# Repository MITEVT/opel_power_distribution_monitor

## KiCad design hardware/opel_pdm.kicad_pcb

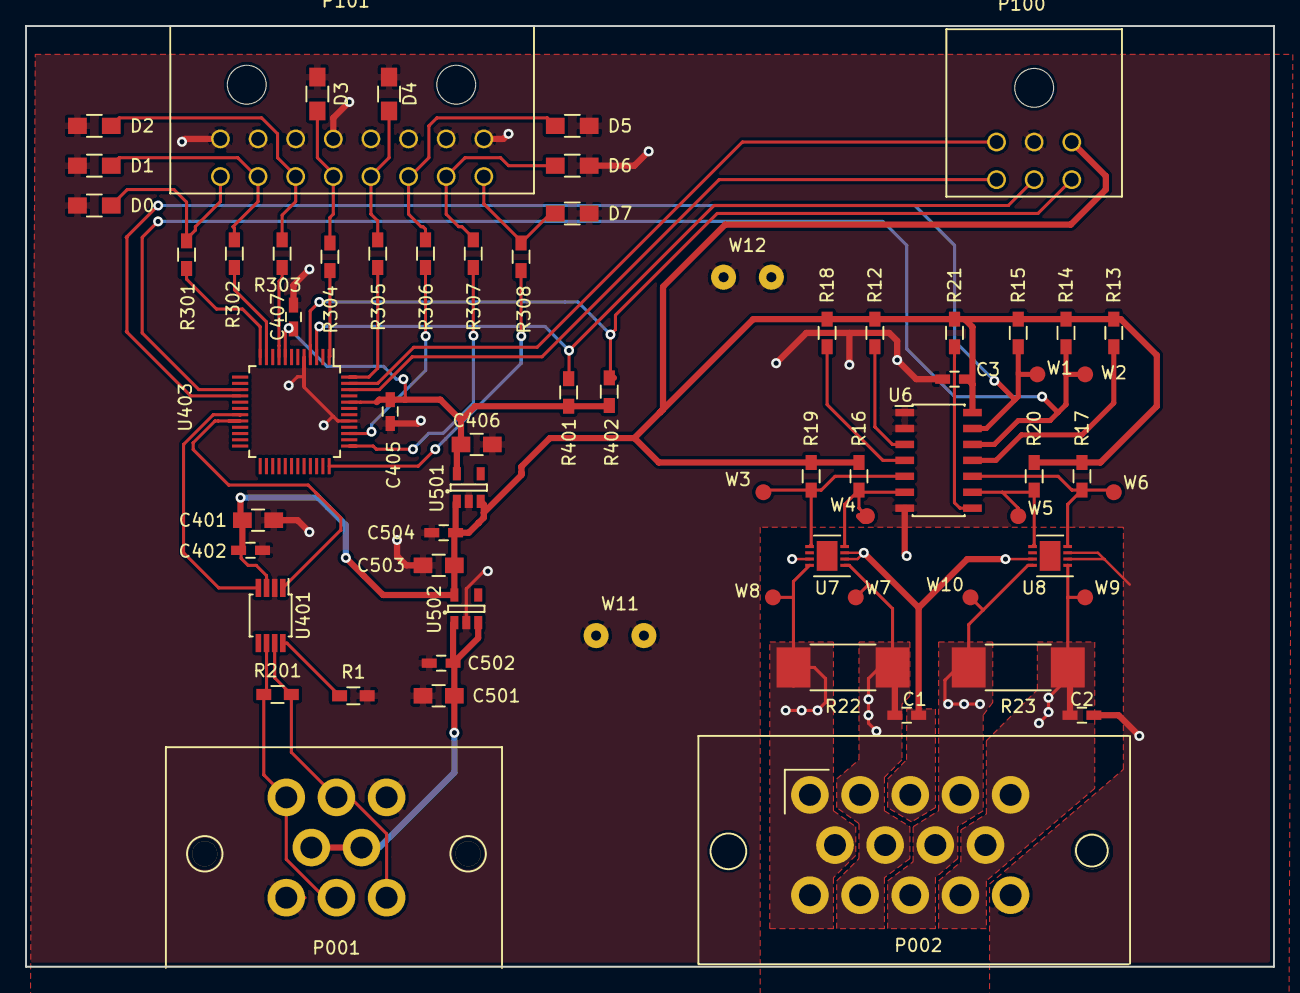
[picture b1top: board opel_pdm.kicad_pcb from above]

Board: 2 copper layers, 99.5 x 75.0 mm, 67 parts (0 on the bottom side), 43 nets.

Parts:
C1, C2: 1uF; C_0603_HandSoldering
C3, C402, C405, C407: 0.1uF; C_0603_HandSoldering
C401, C406: 10uF; C_0805_HandSoldering
C501, C503: 10μ; C_0805_HandSoldering
C502, C504: .1μ; C_0603_HandSoldering
D0: PIO2_8; R_0805_HandSoldering
D1: PIO2_7; R_0805_HandSoldering
D2: PIO1_8; R_0805_HandSoldering
D3: PIO2_6; R_0805_HandSoldering
D4: PIO3_3; R_0805_HandSoldering
D5: PIO1_3; R_0805_HandSoldering
D6: PIO3_1; R_0805_HandSoldering
D7: PIO3_0; R_0805_HandSoldering
P001: CANCONNECTOR; 776280-1
P002: CONN_01X14; 776267-1
P100: ISP; Connector_Microfit3_Header_02x03_Angled_43045-060x
P101: DEBUG_LED; Connector_Microfit3_Header_02x08_Angled_43045-160x
R1: 20k; R_0603_HandSoldering
R12, R13, R14, R15, R16, R17, R18, R19, R20, R21, R401, R402: 10k; R_0603_HandSoldering
R22, R23: 0.002; R_2512_HandSoldering
R201: 120; R_0603_HandSoldering
R301, R302, R303, R304, R305, R306, R307, R308: 100; R_0603_HandSoldering
U6: TCA9543A; SOIC-14_3.9x8.7mm_Pitch1.27mm
U7, U8: LTC2943; DFN-8-1EP_3x3mm_Pitch0.5mm
U401: MCP2551-I/SN; MSOP-8_3x3mm_Pitch0.65mm
U403: LPC11C14; LQFP-48_7x7mm_Pitch0.5mm
U501: MCP1755-33; SOT-23-5
U502: MCP1755-5; SOT-23-5
W1: SDA; smd_test_pad
W2: SCL; smd_test_pad
W3: SD0; smd_test_pad
W4: SC0; smd_test_pad
W5, W6: SD1; smd_test_pad
W7: CS+; smd_test_pad
W8: CS-; smd_test_pad
W9: LV+; smd_test_pad
W10: LV-; smd_test_pad
W11, W12: TST_GND; SolderWirePad_2x_0-8mmDrill

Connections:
+3V3: C405.1, C406.1, C407.1, R401.1, R402.1, U403.8, U403.44, U501.5
+5V: C3.1, C401.1, C402.1, C503.1, C504.1, P100.3, R12.1, R13.1, R14.1, R15.1, R16.1, R17.1, R18.1, R19.1, R20.1, R21.1, U6.14, U401.3, U501.1, U501.3, U502.5
/BACK_PANEL/CANH: P001.2, P001.8, R201.2, U401.7
/BACK_PANEL/CANL: P001.1, P001.7, R201.1, U401.6
/BACK_PANEL/CS_SENSE+: C1.1, P002.2, P002.7, P002.11, R22.1, U7.1, W7.1
/BACK_PANEL/CS_SENSE-: P002.1, P002.6, P002.10, R22.2, U7.8, W8.1
/BACK_PANEL/LV_SENSE+: C2.1, P002.5, P002.9, P002.13, R23.1, U8.1, W9.1
/BACK_PANEL/LV_SENSE-: P002.4, P002.8, P002.12, R23.2, U8.8, W10.1
/FRONT_PANEL/LED0: R301.1, U403.12
/FRONT_PANEL/LED1: R302.2, U403.11
/FRONT_PANEL/LED2: R303.2, U403.9
/FRONT_PANEL/LED3: R304.1, U403.1
/FRONT_PANEL/LED4: R305.2, U403.48
/FRONT_PANEL/LED5: R306.1, U403.39
/FRONT_PANEL/LED6: R307.2, U403.37
/FRONT_PANEL/LED7: R308.1, U403.36
/FRONT_PANEL/MCU_PROG_N: P100.6, R402.2, U403.4
/FRONT_PANEL/MCU_RESET_N: P100.5, R401.2, U403.3
/FRONT_PANEL/RXD: P100.4, U403.46
/FRONT_PANEL/TXD: P100.1, U403.47
/I2C Multiplexer and Gas Gauges/SCL: R14.2, U6.12, U403.15, W2.1
/I2C Multiplexer and Gas Gauges/SDA: R15.2, U6.13, U403.16, W1.1
/Micro_Controller/CAN_RXD: U401.4, U403.19
/Micro_Controller/CAN_TXD: U401.1, U403.20
/Power_Supplies/+12V: C501.2, C502.1, P001.4, P001.5, U502.1, U502.3
GND: C1.2, C2.2, C3.2, C401.2, C402.2, C405.2, C406.2, C407.2, C501.1, C502.2, C503.2, C504.2, D0.1, D1.1, D2.1, D3.1, D4.1, D5.1, D6.1, D7.1, P001.3, P001.6, P002.3, P002.14, P100.2, P101.1, P101.2, P101.3, P101.4, P101.5, P101.6, P101.7, P101.8, R1.2, U6.1, U6.2, U6.7, U7.2, U7.3, U7.7, U8.2, U8.3, U8.7, U401.2, U403.5, U403.41, U501.2, U502.2, W11.1, W12.1
unnamed: D0.2, P101.9, R301.2
unnamed: D1.2, P101.10, R302.1
unnamed: D2.2, P101.11, R303.1
unnamed: D3.2, P101.12, R304.2
unnamed: D4.2, P101.13, R305.1
unnamed: D5.2, P101.14, R306.2
unnamed: D6.2, P101.15, R307.1
unnamed: D7.2, P101.16, R308.2
unnamed: R1.1, U401.8
unnamed: R12.2, U6.3
unnamed: R13.2, U6.11
unnamed: R16.2, U6.6, U7.4, W4.1
unnamed: R17.2, U6.10, U8.4, W6.1
unnamed: R18.2, U6.4
unnamed: R19.2, U6.5, U7.5, W3.1
unnamed: R20.2, U6.9, U8.5, W5.1
unnamed: R21.2, U6.8

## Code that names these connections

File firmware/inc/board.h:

#ifndef __BOARD_H_
#define __BOARD_H_

#include "chip.h"
#include "util.h"
#include <string.h>

// -------------------------------------------------------------
// Global Variables

extern const uint32_t OscRateIn; 
volatile uint32_t msTicks; 						// Running count of milliseconds since start

// -------------------------------------------------------------
// Configuration Macros

typedef struct {
	bool low_voltage_bus_battery;
	bool low_voltage_dc_dc;
	bool critical_systems_bus_battery;
	bool critical_systems_dc_dc;
	bool pdm_on;
	bool mux_on;
	bool lv_on;
	bool cs_on;
} PDM_STATUS_T;

// -------------------------------------------------------------
// Pin Descriptions

#define LED0_PORT 2
#define LED0_PIN 5

#define LED1_PORT 0
#define LED1_PIN 6

#define LED2_PORT 0
#define LED2_PIN 7

#define LED3_PORT 2
#define LED3_PIN 9

#define UART_RX_PORT 1
#define UART_RX_PIN 6
#define UART_RX_IOCON IOCON_PIO1_6

#define UART_TX_PORT 1
#define UART_TX_PIN 7
#define UART_TX_IOCON IOCON_PIO1_7

//PDM
#define LOW_VOLTAGE_THRESHOLD 10000
#define ONE_TICK 1000
#define FREQ_OFFSET 1


// -------------------------------------------------------------
// Computed Macros
#define FREQ_THRESHOLD ONE_TICK/(PDM_PACKET__freq + FREQ_OFFSET)

#define LED0 LED0_PORT, LED0_PIN
#define LED1 LED1_PORT, LED1_PIN
#define LED2 LED2_PORT, LED2_PIN
#define LED3 LED3_PORT, LED3_PIN

#define UART_RX UART_RX_PORT, UART_RX_PIN
#define UART_TX UART_TX_PORT, UART_TX_PIN

#define Board_LED_On(led) {Chip_GPIO_SetPinState(LPC_GPIO, led, true);}
#define Board_LED_Off(led) {Chip_GPIO_SetPinState(LPC_GPIO, led, false);}
 
// -------------------------------------------------------------
// Board Level Function Prototypes

int8_t Board_SysTick_Init(void);

void Board_LEDs_Init(void);

void Board_UART_Init(uint32_t baudrate);

void Board_I2C_Init(void);

/**
 * Reset both gas gauges by writing a given byte to both control registers.
 *
 * @param reset_val the byte with which to overwrite the control registers
 * @param i2c_tx_buffer a pointer to the array to write data through I2C
 */
void Board_I2C_Reset(uint8_t reset_val, uint8_t *i2c_tx_buffer);

/**
 * Send a PDM heartbeat over CAN as defined in the CAN spec.
 *
 * @param *pdm_status a pointer to the current status of the PDM
 * @param *msg_obj a pointer to the CAN message object
 */
void Board_CAN_SendHeartbeat(PDM_STATUS_T *pdm_status, CCAN_MSG_OBJ_T *msg_obj, bool comm_err);

void Board_PDM_Status_Debug(PDM_STATUS_T *pdm_status, bool mux_i2c, bool cs_i2c, bool lv_i2c);

/**
 * Update the struct containing the current status of the PDM.
 * 
 * @param pdm_status the struct to be updated
 * @param i2c_rx_buffer the array to store I2C readings
 * @param cs the tested system; true for critical systems, false for low voltage systems
 * @return true if the PDM successfully communicated through I2C, false otherwise
 */
bool Board_PDM_Status_Update(PDM_STATUS_T *pdm_status, uint8_t *i2c_rx_buffer, bool cs);

/**
 * Transmit the given string through the UART peripheral (blocking)
 * 
 * @param str pointer to string to transmit
 * @note	This function will send or place all bytes into the transmit
 *			FIFO. This function will block until the last bytes are in the FIFO.
 */
void Board_UART_Print(const char *str);

/**
 * Transmit a string through the UART peripheral and append a newline and a linefeed character (blocking)
 * 
 * @param str pointer to string to transmit
 * @note	This function will send or place all bytes into the transmit
 *			FIFO. This function will block until the last bytes are in the FIFO.
 */
void Board_UART_Println(const char *str);

/**
 * Transmit a string containing a number through the UART peripheral (blocking)
 * 
 * @param num number to print
 * @param base number base
 * @param crlf append carraige return and line feed
 */
void Board_UART_PrintNum(const int num, uint8_t base, bool crlf);

/**
 * Transmit a byte array through the UART peripheral (blocking)
 * 
 * @param	data		: Pointer to data to transmit
 * @param	num_bytes	: Number of bytes to transmit
 * @note	This function will send or place all bytes into the transmit
 *			FIFO. This function will block until the last bytes are in the FIFO.
 */
void Board_UART_SendBlocking(const void *data, uint8_t num_bytes);

/**
 * Read data through the UART peripheral (non-blocking)
 * 
 * @param	data		: Pointer to bytes array to fill
 * @param	num_bytes	: Size of the passed data array
 * @return	The actual number of bytes read
 * @note	This function reads data from the receive FIFO until either
 *			all the data has been read or the passed buffer is completely full.
 *			This function will not block. This function ignores errors.
 */
int8_t Board_UART_Read(void *data, uint8_t num_bytes);

void Board_CAN_Init(uint32_t baudrate, void (*rx_callback)(uint8_t), void (*tx_callback)(uint8_t), void (*error_callback)(uint32_t));


#endif

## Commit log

2015-11-14 Updated gitignore
2015-11-14 Initial firmware commit
2015-11-14 Created basic PDM logic with switches. Fuck you.
2015-11-14 Fixed board.c and board.h. Moved around locations of Pin initialization. Fuck you.
2015-11-21 Now sends CAN messages instead of UART.
2016-01-16 Added I2C initialization and read/write functionality. Currently broken.
2016-01-20 Updated CAN messaging to match the CAN specification.
2016-01-27 Implemented working I2C code to read data from gas gauge.
2016-01-29 Implemented I2C to successfully measure battery current and state of charge.
2016-02-06 Added I2C multiplexer code.
    Implemented I2C channel switching with two channels.
    Updated CAN messaging logic.
    Added pdm shutdown logic.
2016-02-10 Cleaned up code, fixed PDM shutdown logic.
2016-02-13 Added PCB design elements.
    Implemented LED debugging.
    Added Kicad schematic for PDM.
    Laid out schematic for I2C multiplexer and two gas gauges.
2016-02-26 Fixed renaming issue in schematic, laid out components in pcb.
2016-02-27 Finished laying out PCB and completed traces.
2016-02-27 Finished PCB layout for real this time.
2016-02-27 Fixed shutdown logic and LED issues.
2016-03-12 Fixed connector spacing.
2016-04-02 Changed gas gauges to reset upon power disconnection. Cleaned up code.
2016-04-09 Cleaned up and commented code.
2016-04-16 Fixed multiple PCB issues.
    Fixed track widths.
    Added decoupling capacitor for multiplexer.
    Added additional vias to ground plane.
    Replaced traces with zones for high current connector inputs.
    Added additional input for sense input and ground input to connector.
    Removed 10V voltage regualator and associated circuitry.
2016-04-16 Deleted track fragments.
2016-04-16 Fixed connector zone spacing, added vias to back plate.
2016-04-23 Cleaned up PCB, changed via/zone spacings.
2016-04-23 Added I2C and CAN header files.
2016-04-23 Updated variable names.
2016-04-23 Renamed i2c header file.
2016-04-30 Renamed PDM hardware files.
2016-10-22 Added LEDs and another decoupling capacitor to board.
2016-10-29 Added test points, LEDs, 3D model to board.
2016-10-30 Added error protocols.
2016-11-19 Modularized code for readability and testing.
2016-11-19 Changed order of CAN message to match CAN spec.
2017-02-18 created fake PDM module
2017-03-04 Updates to test bench configuration
